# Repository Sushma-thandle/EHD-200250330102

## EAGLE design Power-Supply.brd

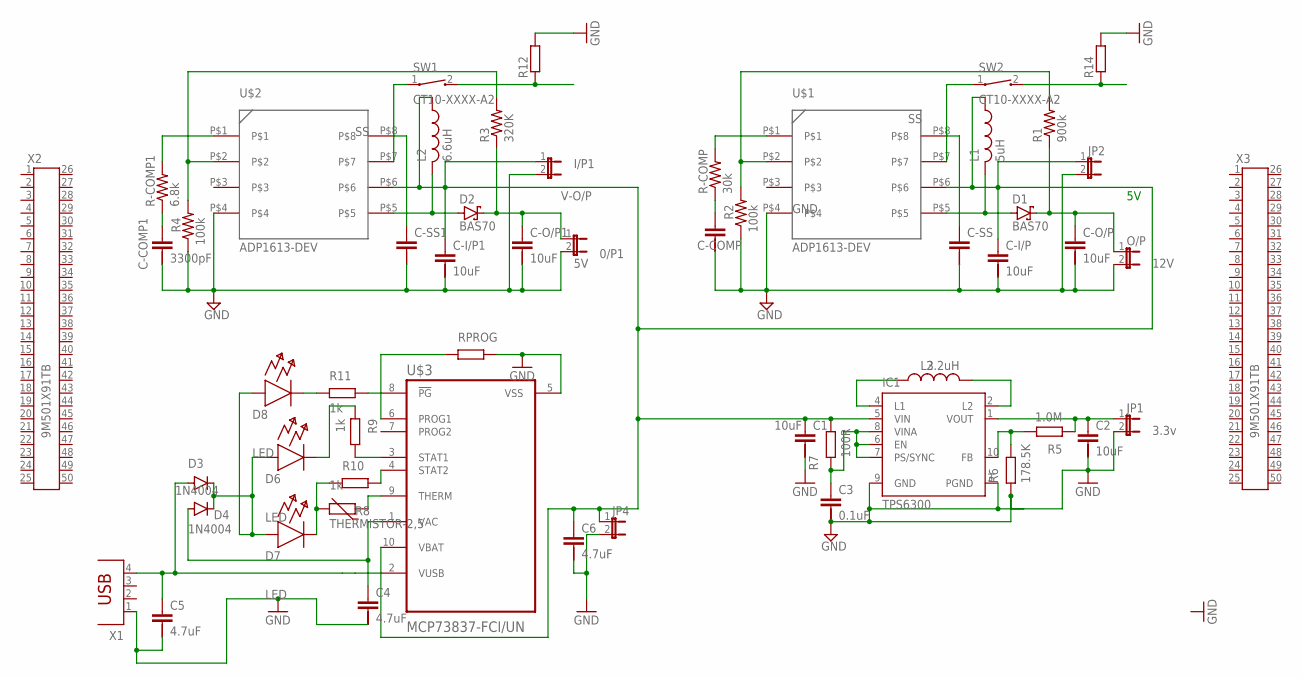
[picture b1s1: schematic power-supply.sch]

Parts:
0/P1: 5V; JP1
C1, C2: 10uF; C2.5/5-2
C3: 0.1uF; C2.5/5-2
C4, C5, C6: 4.7uF; C2.5/5-2
C-COMP: C-2.5-5/2; C2.5/5-2
C-COMP1: 3300pF; C2.5/5-2
C-I/P, C-I/P1: 10uF; C2.5/5-2
C-O/P, C-O/P1: 10uF; C2.5/5-2
C-SS, C-SS1: C-2.5-5/2; C2.5/5-2
D1, D2: BAS70; SOT23
D3, D4: 1N4004; DO41-10
I/P1: 3.3V; JP1
IC1: TPS6300; DRC-S-PVSON-N10
JP1: 3.3v; JP1
JP2, JP4: JP1E; JP1
L1: 5uH; 0204/5
L2: 6.6uH; 0204/5
L3: 2.2uH; 0204/5
O/P: 12V; JP1
R1: 900k; 0204V
R2, R4: 100k; 0204V
R3: 320K; 0204V
R8: THERMISTOR-2,5; RS-2,5
R12, R14: R-EU_0204/2V; 0204V
R-COMP: 30k; 0204V
R-COMP1: 6.8k; 0204V
SW1, SW2: CT10-XXXX-A2
U$1, U$2: ADP1613-DEV; ADP1613-FOOTPRINT
U$3: MCP73837-FCI/UN; SOP50P490X110-10N
X1: PN87520
X2, X3: 9M501X91TB; 9M501X91

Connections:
unnamed: D1.1 (A), L1.2, U$1.P$5
unnamed: SW1.1, U$2.P$7
unnamed 2: C1.1, C6.1, C-I/P.1, C-I/P1.1, I/P1.1, IC1.5 (VIN), JP2.1, JP4.1, L1.1, L2.1, U$1.P$6, U$2.P$6, U$3.10 (VBAT); also elsewhere on the board
unnamed: C-COMP.1, R-COMP.1
unnamed: R-COMP1.2, U$2.P$1
unnamed: R-COMP.2, U$1.P$1
unnamed: IC1.4 (L1), L3.1
unnamed: C-COMP1.1, R-COMP1.1
unnamed: IC1.2 (L2), L3.2
unnamed: D2.1 (A), L2.2, U$2.P$5
unnamed 10: C2.1, IC1.1 (VOUT), JP1.1; also elsewhere on the board
unnamed 11: IC1.10 (FB); also elsewhere on the board
unnamed: R12.1, SW1.2
unnamed 13: C3.1, IC1.6 (EN), IC1.7 (PS/SYNC), IC1.8 (VINA); also elsewhere on the board
unnamed: SW2.1, U$1.P$7
unnamed 19: D3.C, D4.C; also elsewhere on the board
unnamed 21: R8.2; also elsewhere on the board
unnamed: C5.1, D3.A, U$3.2 (VUSB), X1.4
unnamed 23: U$3.6 (PROG1); also elsewhere on the board
unnamed: C4.1, D4.A, U$3.1 (VAC)
unnamed: R8.1, U$3.9 (THERM)
unnamed: R14.1, SW2.2
SS: C-SS.1, C-SS1.1, U$1.P$8, U$2.P$8
V-I/P: R3.2, R4.2, U$2.P$2
V-O/P: 0/P1.1, C-O/P1.1, D2.3 (C), R3.1
VIN: R1.2, R2.2, U$1.P$2
VOP: C-O/P.1, D1.3 (C), O/P.1, R1.1

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
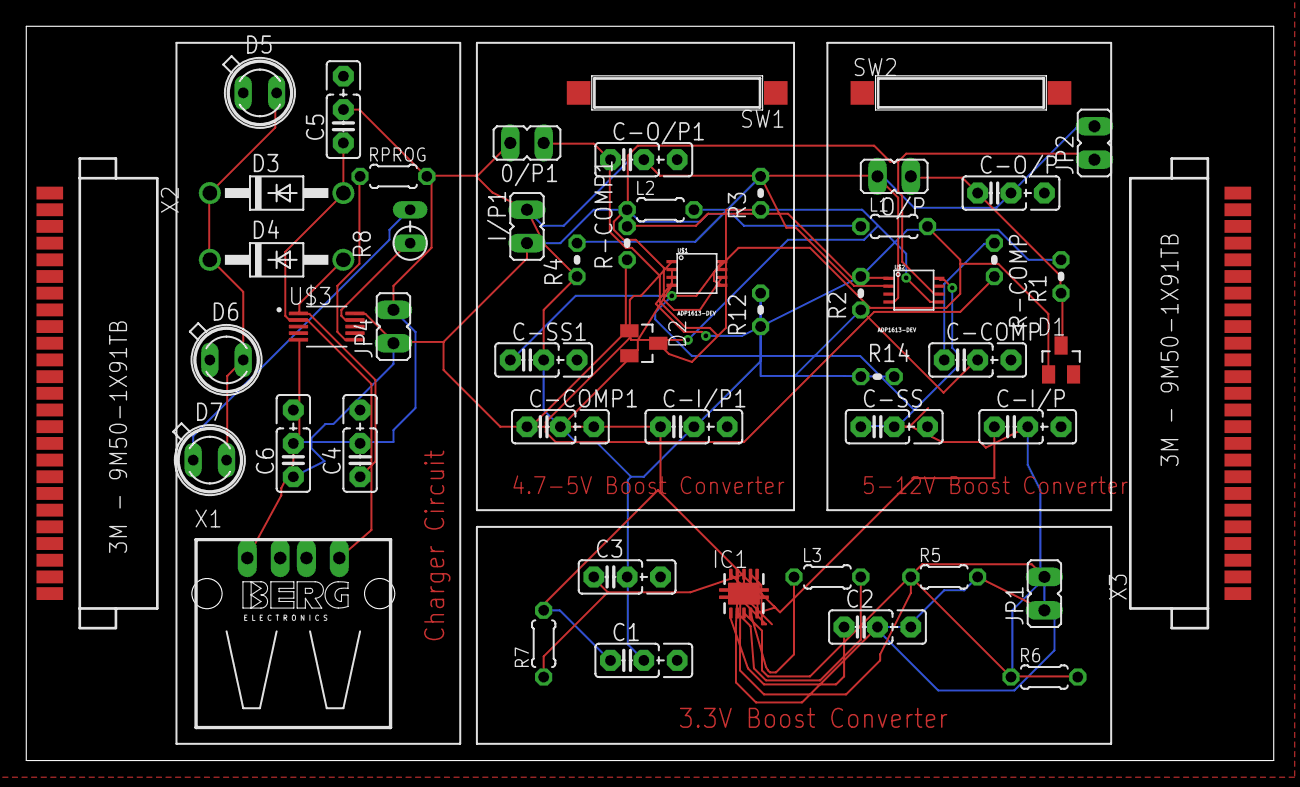
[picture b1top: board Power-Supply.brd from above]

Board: 2 copper layers, 94.9 x 55.9 mm, 52 parts (0 on the bottom side), 29 nets.

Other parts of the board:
D5, D6, D7: SFH482
R5: 1.0M; 0204/5
R6: 178.5K; 0204/5
R7: 100R; 0204/5
RPROG: 0204/5

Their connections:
unnamed 2: R7.2; also elsewhere on the board
unnamed 10: R5.2; also elsewhere on the board
unnamed 11: R5.1, R6.2; also elsewhere on the board
unnamed 13: R7.1; also elsewhere on the board
unnamed 19: D5.K, D6.K, D7.K; also elsewhere on the board
unnamed 21: D7.A; also elsewhere on the board
unnamed 23: RPROG.1; also elsewhere on the board

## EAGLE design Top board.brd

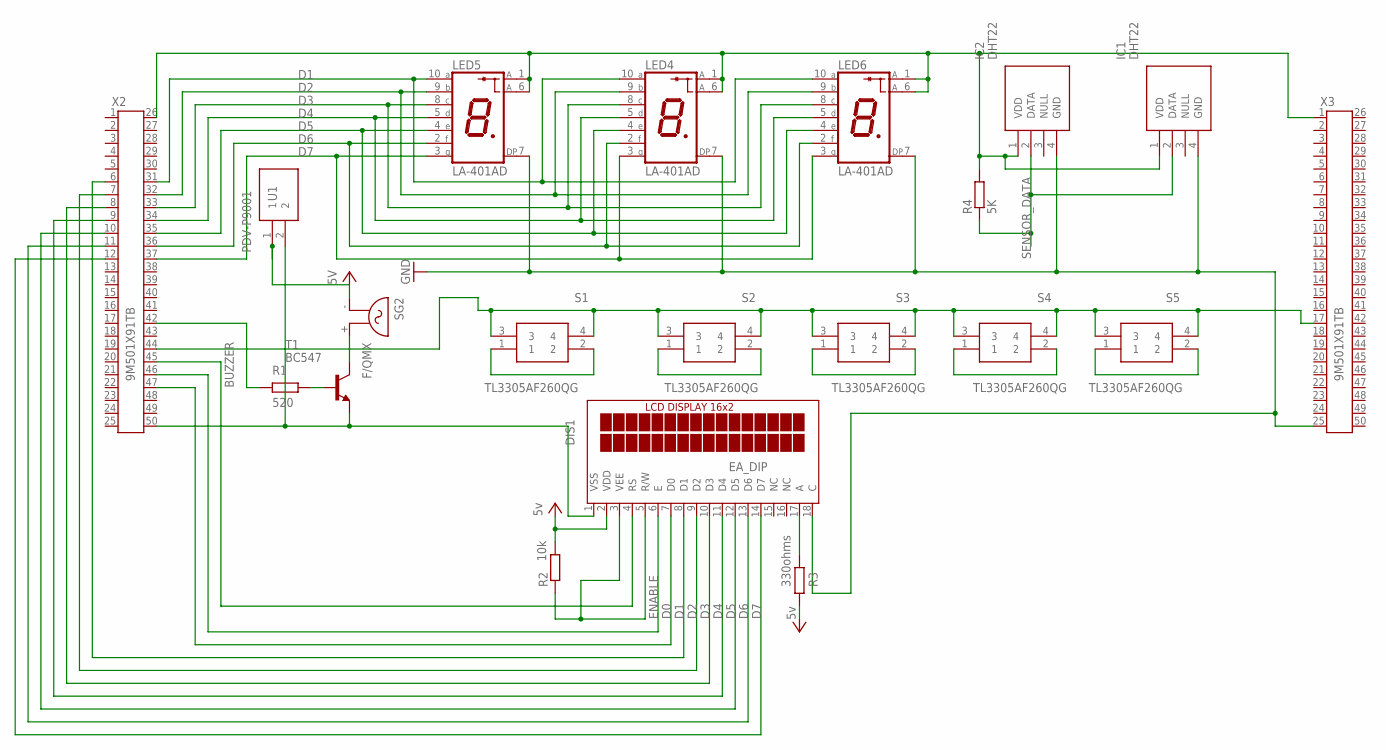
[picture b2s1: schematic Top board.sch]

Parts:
DIS1: EA_DIP
IC1, IC2: DHT22
LED4, LED5, LED6: LA-401AD; LA-401
R2: 10k; 0204V
R3: 330ohms; 0204V
R4: 5K; 0204V
S1, S2, S3, S4, S5: TL3305AF260QG; TL3305AF160QG
SG2: F/QMX
T1: BC547; TO92
U1: PDV-P9001; PDVP9001
X2, X3: 9M501X91TB; 9M501X91

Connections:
BUZZER: X2.42
D0: DIS1.7 (D0), X2.47
D1: DIS1.8 (D1), LED4.10 (A), LED5.10 (A), LED6.10 (A), X2.6, X2.31
D2: DIS1.9 (D2), LED4.9 (B), LED5.9 (B), LED6.9 (B), X2.7, X2.32
D3: DIS1.10 (D3), LED4.8 (C), LED5.8 (C), LED6.8 (C), X2.8, X2.33
D4: DIS1.11 (D4), LED4.5 (D), LED5.5 (D), LED6.5 (D), X2.9, X2.34
D5: DIS1.12 (D5), LED4.4 (E), LED5.4 (E), LED6.4 (E), X2.10, X2.35
D6: DIS1.13 (D6), LED4.2 (F), LED5.2 (F), LED6.2 (F), X2.11, X2.36
D7: DIS1.14 (D7), LED4.3 (G), LED5.3 (G), LED6.3 (G), X2.12, X2.37
ENABLE: DIS1.6 (E), X2.46
GND: DIS1.18 (C), IC1.4 (GND), IC2.4 (GND), LED4.7 (DP), LED5.7 (DP), LED6.7 (DP), X3.25
unnamed: SG2.+ (2), T1.3 (C)
unnamed: DIS1.4 (RS), X2.45
unnamed: DIS1.3 (VEE), DIS1.5 (R/W), R2.1
unnamed: DIS1.1 (VSS), T1.1 (E), U1.2, X2.50
unnamed: S1.3, S1.4, S2.3, S2.4, S3.3, S3.4, S4.3, S4.4, S5.3, S5.4, X2.44, X3.17
unnamed: IC1.1 (VDD), IC2.1 (VDD), LED4.1 (A), LED4.6 (A), LED5.1 (A), LED5.6 (A), LED6.1 (A), LED6.6 (A), R4.2, X2.26, X3.1
unnamed: S1.1, S1.2
unnamed: DIS1.17 (A), R3.2
unnamed: S2.1, S2.2
unnamed: S3.1, S3.2
unnamed: S4.1, S4.2
unnamed: S5.1, S5.2
SENSOR_DATA: IC1.2 (DATA), IC2.2 (DATA), R4.1
VCC: DIS1.2 (VDD), R2.2, R3.1, SG2.- (1), U1.1

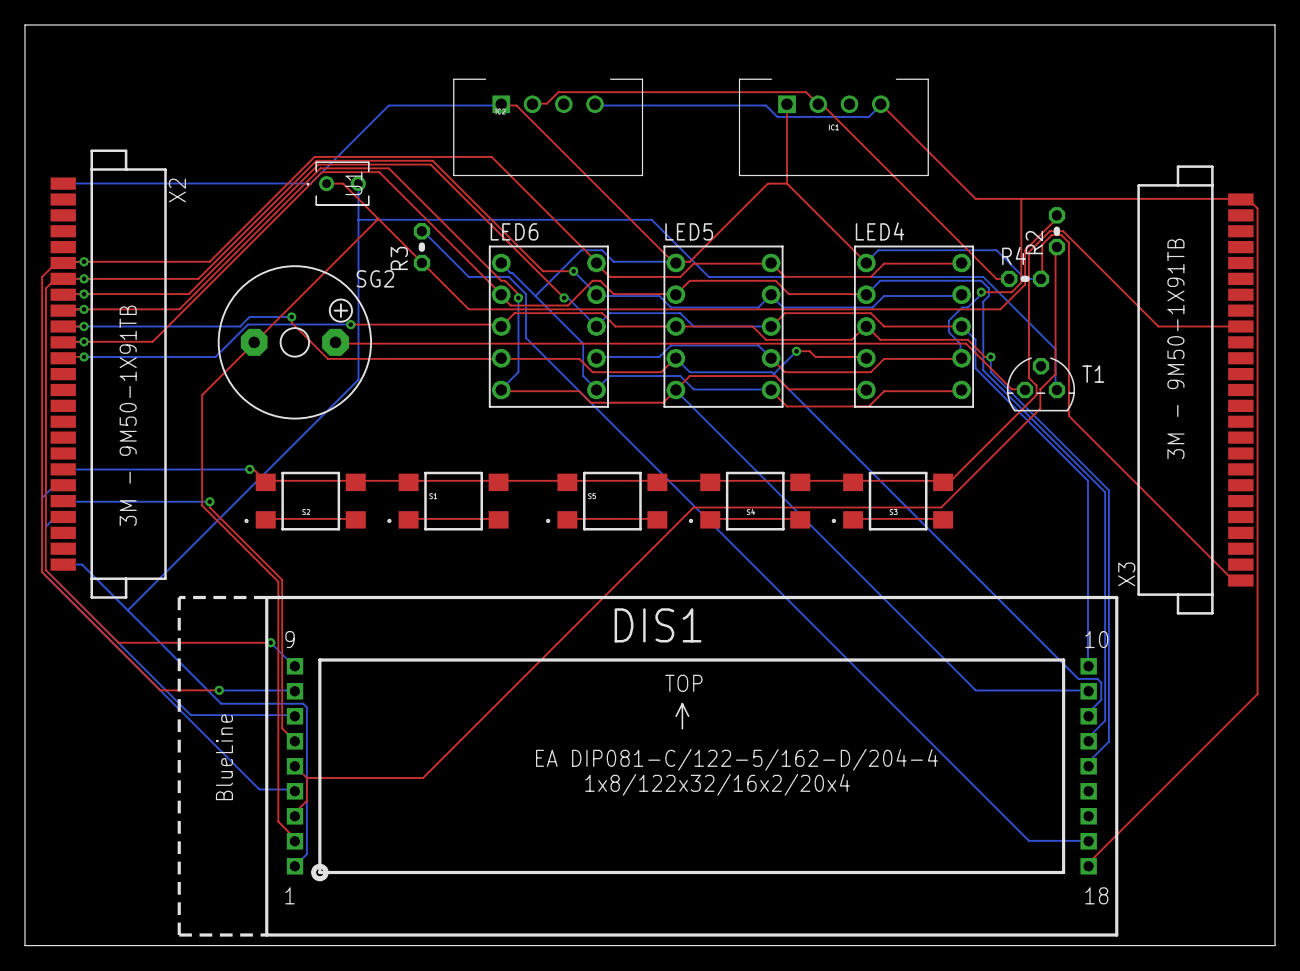
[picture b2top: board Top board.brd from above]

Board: 2 copper layers, 100.0 x 73.7 mm, 19 parts (0 on the bottom side), 24 nets.

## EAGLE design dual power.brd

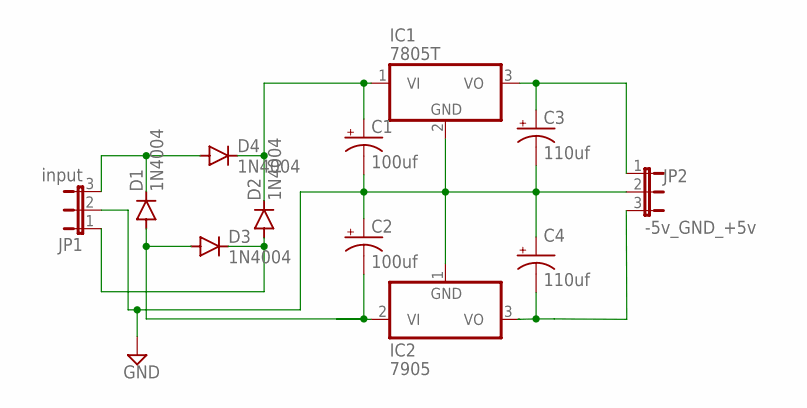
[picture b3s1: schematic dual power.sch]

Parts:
C1, C2: 100uf; 085CS_1AR
C3, C4: 110uf; 085CS_1AR
D1, D2, D3, D4: 1N4004; DO41-10
IC1: 7805T; TO220H
IC2: 7905; TO220H
JP1: input; JP2
JP2: -5v_GND_+5v; JP2

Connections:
GND: C1.-, C2.+, C3.-, C4.+, IC1.2 (GND), IC2.1 (GND), JP1.2, JP2.2
unnamed: D1.C, D4.A, JP1.3
unnamed: C1.+, D2.C, D4.C, IC1.1 (VI)
unnamed: C2.-, D1.A, D3.A, IC2.2 (VI)
unnamed: D2.A, D3.C, JP1.1
unnamed: C3.+, IC1.3 (VO), JP2.1
unnamed: C4.-, IC2.3 (VO), JP2.3

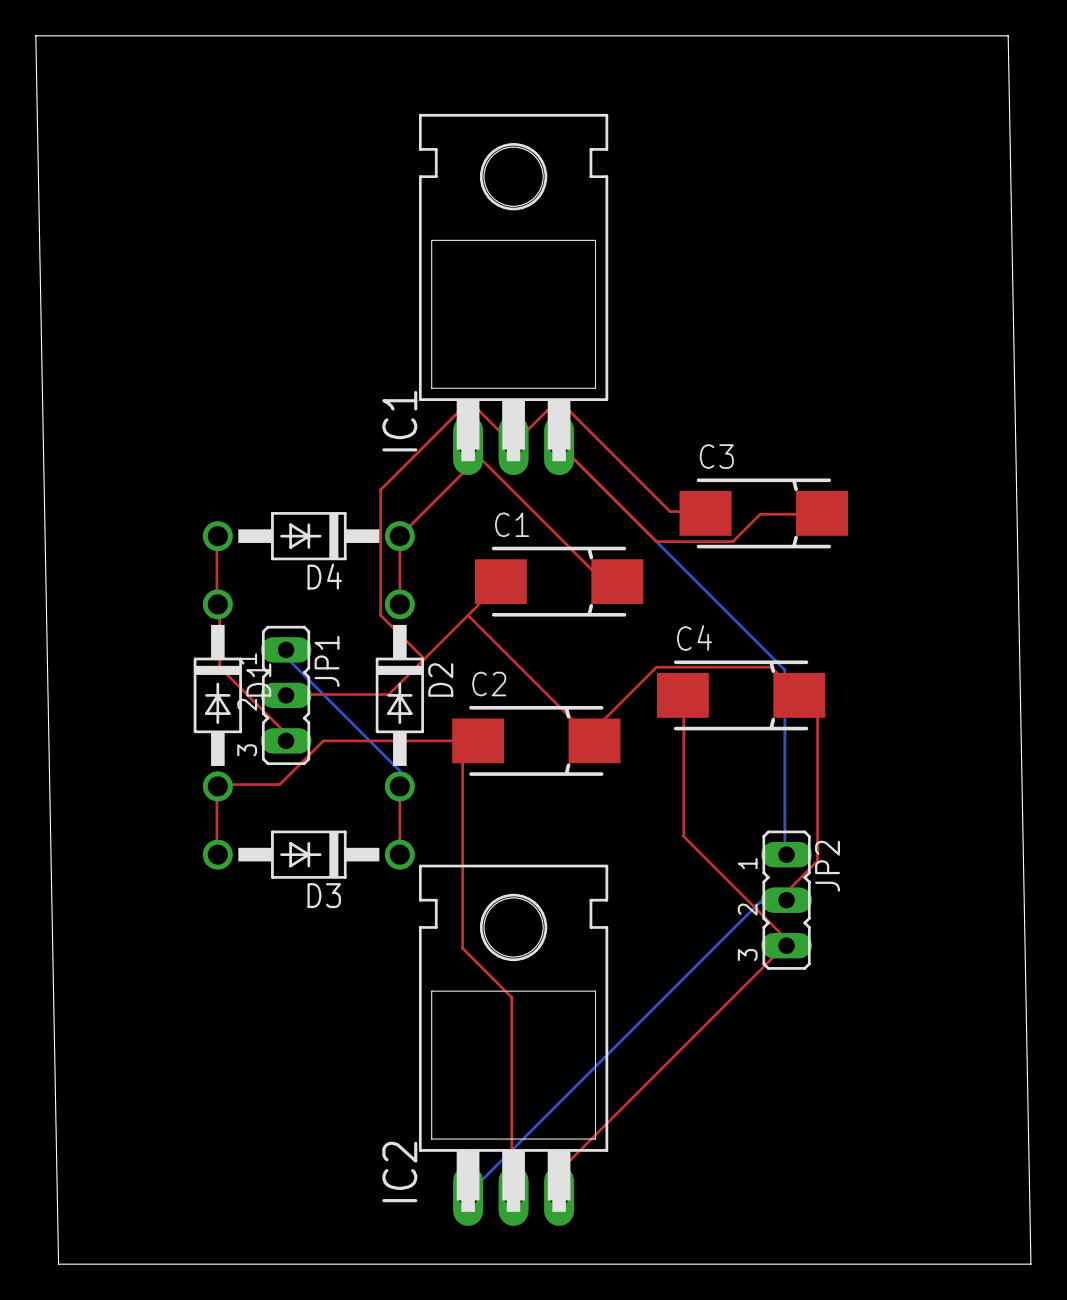
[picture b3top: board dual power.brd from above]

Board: 2 copper layers, 55.5 x 68.6 mm, 12 parts (0 on the bottom side), 7 nets.

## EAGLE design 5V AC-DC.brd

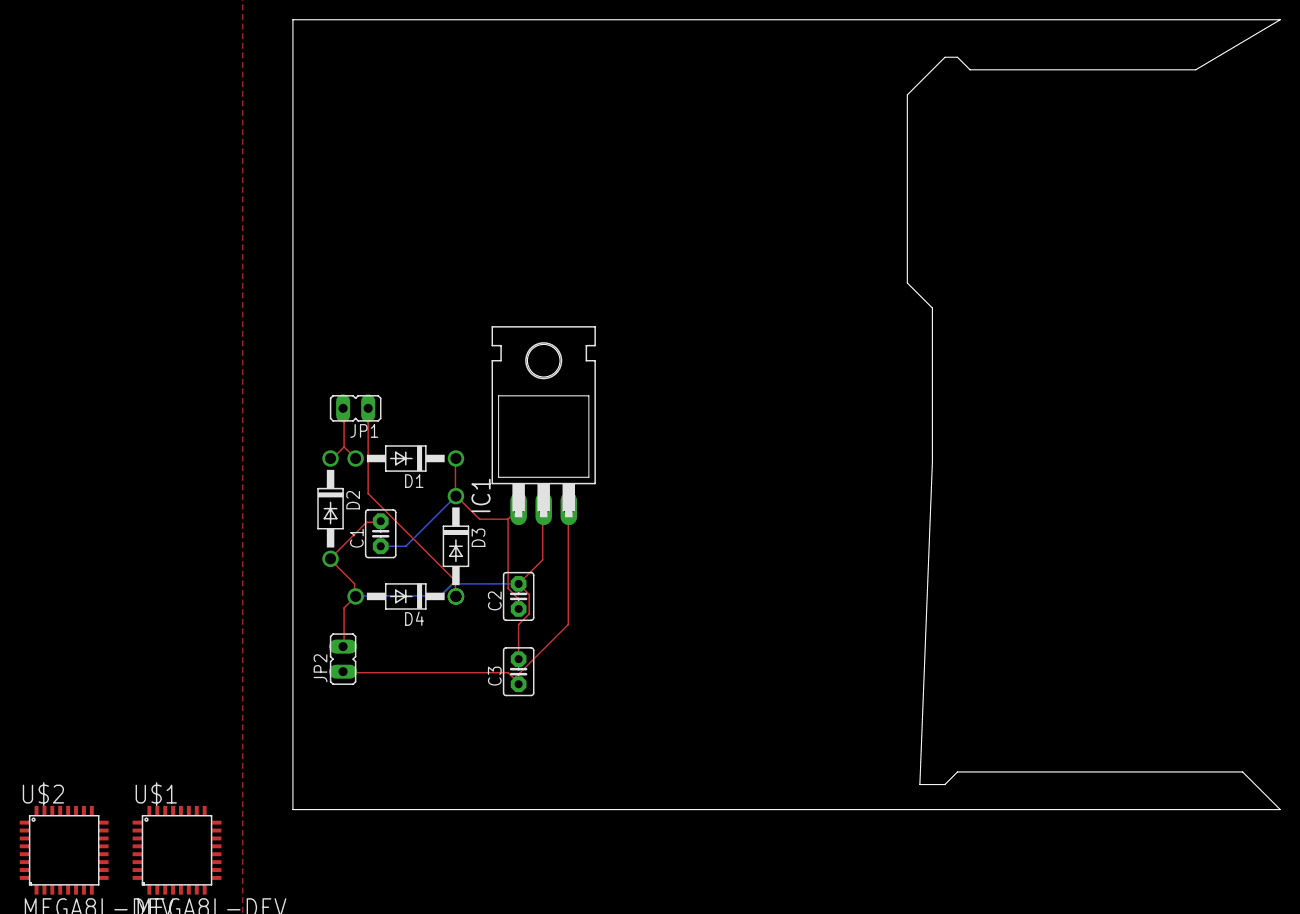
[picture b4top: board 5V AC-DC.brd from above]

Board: 2 copper layers, 100.0 x 80.0 mm, 12 parts (0 on the bottom side), 37 nets.

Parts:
C1: 100uF; C2.5-3
C2: 0.33uF; C2.5-3
C3: 0.1uF; C2.5-3
D1, D2, D3, D4: 1N4004; DO41-10
IC1: 7805T; TO220H
JP1: 12v AC; JP1
JP2: 5V DC; JP1
U$1, U$2: MEGA8L-DEV; TQFP-MEGA8L

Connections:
GND: C1.2, C2.2, C3.2, D2.A, D4.A, IC1.2, JP2.2
unnamed: D1.A, D2.C, JP1.2
unnamed: C1.1, C2.1, D1.C, D3.C, IC1.1
unnamed: U$1.P$1, U$2.P$1
unnamed: D3.A, D4.C, JP1.1
unnamed: U$1.P$2, U$2.P$2
unnamed: C3.1, IC1.3, JP2.1
unnamed: U$1.P$3, U$2.P$3
unnamed: U$1.P$4, U$2.P$4
unnamed: U$1.P$5, U$2.P$5
unnamed: U$1.P$6, U$2.P$6
unnamed: U$1.P$7, U$2.P$7
unnamed: U$1.P$8, U$2.P$8
unnamed: U$1.P$9, U$2.P$9
unnamed: U$1.P$10, U$2.P$10
unnamed: U$1.P$11, U$2.P$11
unnamed: U$1.P$12, U$2.P$12
unnamed: U$1.P$13, U$2.P$13
unnamed: U$1.P$14, U$2.P$14
unnamed: U$1.P$15, U$2.P$15
unnamed: U$1.P$16, U$2.P$16
unnamed: U$1.P$17, U$2.P$17
unnamed: U$1.P$18, U$2.P$18
unnamed: U$1.P$19, U$2.P$19
unnamed: U$1.P$20, U$2.P$20
unnamed: U$1.P$21, U$2.P$21
unnamed: U$1.P$22, U$2.P$22
unnamed: U$1.P$23, U$2.P$23
unnamed: U$1.P$24, U$2.P$24
unnamed: U$1.P$25, U$2.P$25
unnamed: U$1.P$26, U$2.P$26
unnamed: U$1.P$27, U$2.P$27
unnamed: U$1.P$28, U$2.P$28
unnamed: U$1.P$29, U$2.P$29
unnamed: U$1.P$30, U$2.P$30
unnamed: U$1.P$31, U$2.P$31
unnamed: U$1.P$32, U$2.P$32

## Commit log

2020-10-20 Pid and PPid demo
2020-10-20 fork-creation of new process
2020-10-21 program of syslib demo
2020-10-21 syscalldemo
2020-10-21 Buffio demo
2020-10-21 File descriptors demo stdin,stdout,stderr
2020-10-21 forksharing
2020-10-22 Demo for pipes IPC
2020-10-22 FIFO Demo
2020-10-22 Thread demo
2020-10-22 thread global demo
2020-10-23 racecondition demo
2020-10-23 Demo of program vs process
2020-10-23 Demo for makefile
2020-10-23 makefile was enhanced to compile for x86 and arm
2020-10-23 creating libraries demo
2020-10-23 staticlib and dynamiclib
2020-10-28 Modified racecondition
2020-11-23 signalling semaphore,zombie process
2020-11-23 futex and recursive mutex
2020-11-23 Demonstration on mutual exclusion semphore and deadlock
2020-11-23 signalling semaphore
2020-11-23 readwritelocks
2020-11-23 barrier demo
2020-11-23 conditional variable
2020-11-24 Read write demo and shared memory demo
2020-11-24 Message queues
